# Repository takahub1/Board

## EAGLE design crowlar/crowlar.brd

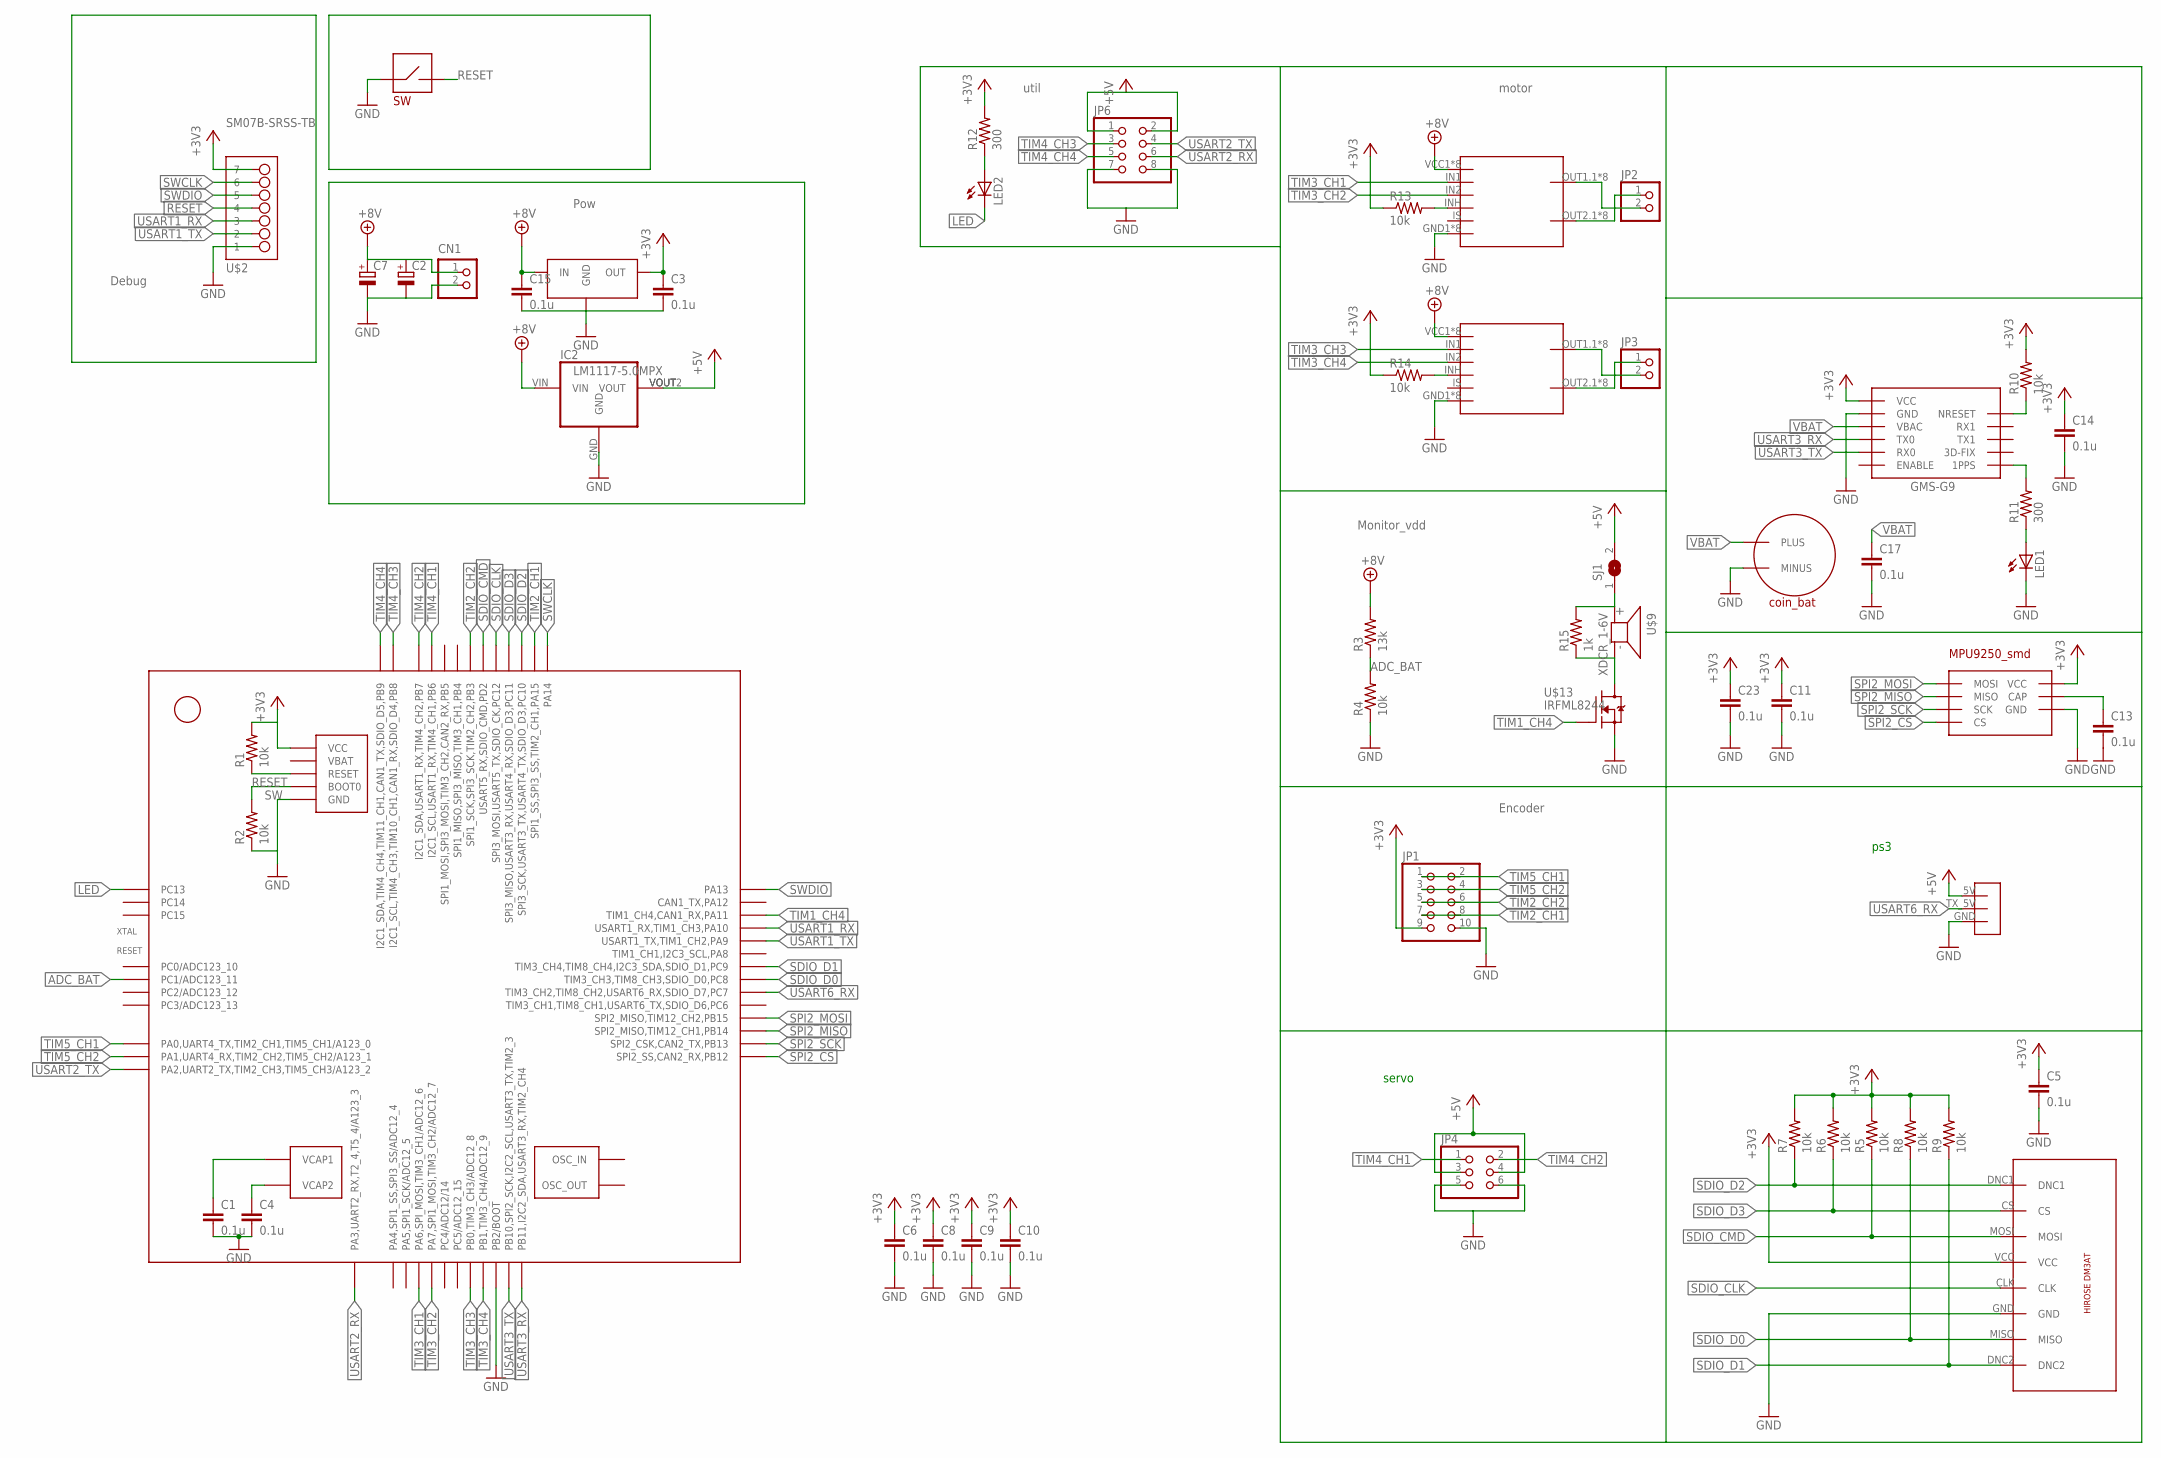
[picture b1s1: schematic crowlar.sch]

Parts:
C1, C3, C4, C5, C6, C8, C9, C10, C11, C13, C14, C15, C17, C23: 0.1u; C0603K
C2, C7: CPOL-EU153CLV-0605; 153CLV-0605
CN1: S2B-XASK-1
IC2: LM1117-5.0MPX; SOT223
JP1: PINHD-2X5/90; 2X05/90
JP2, JP3: PINHD-1X2/90; 1X02/90
JP4: PINHD-2X3/90; 2X03/90
JP6: PINHD-2X4/90; 2X04/90
LED1, LED2: LEDCHIP-LED0603; CHIP-LED0603
R1, R2, R4, R5, R6, R7, R8, R9, R10, R13, R14: 10k; R0603
R3: 13k; R0603
R11, R12: 300; R0603
R15: 1k; R0603
SJ1: SJ
STM32F405RGT6: STM32F405_T; LQFP64
U$1: GMS-G9
U$2: SM07B-SRSS-TB
U$3: SBDBT_5V
U$4, U$11: BTM7752
U$5: DM3AT
U$6: SWTVBP06-B043CB-B; SW
U$8: AP7361-33E; SOT223
U$9: XDCR_1-6V
U$10: 36-3030-ND
U$13: IRFML8244; SOT23
U$16: MPU9250_SMD

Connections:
+3V3: C3.1, C5.1, C6.1, C8.1, C9.1, C10.1, C11.1, C14.1, C23.1, JP1.9, R1.2, R5.2, R6.2, R7.2, R8.2, R9.2, R10.2, R12.2, R13.1, R14.1, STM32F405RGT6.13 (VCC), STM32F405RGT6.19 (VCC), STM32F405RGT6.32 (VCC), STM32F405RGT6.48 (VCC), STM32F405RGT6.64 (VCC), U$1.VCC, U$2.P$7 (7), U$5.VCC, U$8.OUT, U$16.RESV (VCC), U$16.VDD (VCC), U$16.VDDIO (VCC)
+5V: IC2.VOUT, IC2.VOUT2 (VOUT), JP4.3, JP4.4, JP6.1, JP6.2, SJ1.2, U$3.5V
+8V: C2.+, C7.+, C15.1, CN1.1, IC2.VIN, R3.2, U$4.VCC1 (VCC), U$4.VCC2 (VCC), U$4.VCC3 (VCC), U$4.VCC4 (VCC), U$4.VCC5 (VCC), U$4.VCC6 (VCC), U$4.VCC7 (VCC), U$4.VCC8 (VCC), U$8.IN, U$11.VCC1 (VCC), U$11.VCC2 (VCC), U$11.VCC3 (VCC), U$11.VCC4 (VCC), U$11.VCC5 (VCC), U$11.VCC6 (VCC), U$11.VCC7 (VCC), U$11.VCC8 (VCC)
ADC_BAT: R3.1, R4.2, STM32F405RGT6.9 (PC1/ADC123_11)
GND: C1.2, C2.-, C3.2, C4.2, C5.2, C6.2, C7.-, C8.2, C9.2, C10.2, C11.2, C13.2, C14.2, C15.2, C17.2, C23.2, CN1.2, IC2.GND, JP1.10, JP4.5, JP4.6, JP6.7, JP6.8, LED1.C, R2.1, R4.1, STM32F405RGT6.12 (GND), STM32F405RGT6.18 (GND), STM32F405RGT6.28 (PB2/BOOT), STM32F405RGT6.63 (GND), U$1.GND, U$1.GND1 (GND), U$2.P$1 (1), U$3.GND, U$4.GND1 (GND), U$4.GND2 (GND), U$4.GND3 (GND), U$4.GND4 (GND), U$4.GND5 (GND), U$4.GND6 (GND), U$4.GND7 (GND), U$4.GND8 (GND), U$5.GND, U$6.P$1, U$8.GND1 (GND), U$8.GND2 (GND), U$10.MINUS, U$11.GND1 (GND), U$11.GND2 (GND), U$11.GND3 (GND), U$11.GND4 (GND), U$11.GND5 (GND), U$11.GND6 (GND), U$11.GND7 (GND), U$11.GND8 (GND), U$13.2 (S), U$16.GND, U$16.~RESV (GND)
LED: LED2.C, STM32F405RGT6.2 (PC13)
unnamed: JP2.1, U$4.OUT2.1 (OUT2), U$4.OUT2.2 (OUT2), U$4.OUT2.3 (OUT2), U$4.OUT2.4 (OUT2), U$4.OUT2.5 (OUT2), U$4.OUT2.6 (OUT2), U$4.OUT2.7 (OUT2), U$4.OUT2.8 (OUT2)
unnamed: R14.2, U$11.INH
unnamed: R13.2, U$4.INH
unnamed: JP2.2, U$4.OUT1.1 (OUT1), U$4.OUT1.2 (OUT1), U$4.OUT1.3 (OUT1), U$4.OUT1.4 (OUT1), U$4.OUT1.5 (OUT1), U$4.OUT1.6 (OUT1), U$4.OUT1.7 (OUT1), U$4.OUT1.8 (OUT1)
unnamed: C4.1, STM32F405RGT6.47 (VCAP2)
unnamed: C1.1, STM32F405RGT6.31 (VCAP1)
unnamed: R15.2, SJ1.1, U$9.PLUS
unnamed: R15.1, U$9.MINUS (2), U$13.3 (D)
unnamed: JP3.2, U$11.OUT1.1 (OUT1), U$11.OUT1.2 (OUT1), U$11.OUT1.3 (OUT1), U$11.OUT1.4 (OUT1), U$11.OUT1.5 (OUT1), U$11.OUT1.6 (OUT1), U$11.OUT1.7 (OUT1), U$11.OUT1.8 (OUT1)
unnamed: R10.1, U$1.NRESET
unnamed: R11.2, U$1.1PPS
unnamed: LED1.A, R11.1
unnamed: LED2.A, R12.1
unnamed: JP3.1, U$11.OUT2.1 (OUT2), U$11.OUT2.2 (OUT2), U$11.OUT2.3 (OUT2), U$11.OUT2.4 (OUT2), U$11.OUT2.5 (OUT2), U$11.OUT2.6 (OUT2), U$11.OUT2.7 (OUT2), U$11.OUT2.8 (OUT2)
unnamed: C13.1, U$16.REGOUT (CAP)
RESET: R1.1, STM32F405RGT6.7 (RESET), U$2.P$4 (4), U$6.P$2
SDIO_CLK: STM32F405RGT6.53 (SPI3_MOSI,USART5_TX,SDIO_CK,PC12), U$5.CLK
SDIO_CMD: R5.1, STM32F405RGT6.54 (USART5_RX,SDIO_CMD,PD2), U$5.MOSI
SDIO_D0: R8.1, STM32F405RGT6.39 (TIM3_CH3,TIM8_CH3,SDIO_D0,PC8), U$5.MISO
SDIO_D1: R9.1, STM32F405RGT6.40 (TIM3_CH4,TIM8_CH4,I2C3_SDA,SDIO_D1,PC9), U$5.DNC2
SDIO_D2: R7.1, STM32F405RGT6.51 (SPI3_SCK,USART3_TX,USART4_TX,SDIO_D3,PC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), U$5.DNC1
SDIO_D3: R6.1, STM32F405RGT6.52 (SPI3_MISO,USART3_RX,USART4_RX,SDIO_D3,P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), U$5.CS
SPI2_CS: STM32F405RGT6.33 (SPI2_SS,CAN2_RX,PB12), U$16.CS
SPI2_MISO: STM32F405RGT6.35 (SPI2_MISO,TIM12_CH1,PB14), U$16.MISO
SPI2_MOSI: STM32F405RGT6.36 (SPI2_MISO,TIM12_CH2,PB15), U$16.MOSI
SPI2_SCK: STM32F405RGT6.34 (SPI2_CSK,CAN2_TX,PB13), U$16.SCK
SW: R2.2, STM32F405RGT6.60 (BOOT0)
SWCLK: STM32F405RGT6.49 (PA14), U$2.P$6 (6)
SWDIO: STM32F405RGT6.46 (PA13), U$2.P$5 (5)
TIM1_CH4: STM32F405RGT6.44 (TIM1_CH4,CAN1_RX,PA11), U$13.1 (G)
TIM2_CH1: JP1.7, JP1.8, STM32F405RGT6.50 (SPI1_SS,SPI3_SS,TIM2_CH1,PA15)
TIM2_CH2: JP1.5, JP1.6, STM32F405RGT6.55 (SPI1_SCK,SPI3_SCK,TIM2_CH2,PB3)
TIM3_CH1: STM32F405RGT6.22 (PA6,SPI_MOSI,TIM3_CH1/ADC12_6), U$4.IN1
TIM3_CH2: STM32F405RGT6.23 (PA7,SPI1_MOSI,TIM3_CH2/ADC12_7), U$4.IN2
TIM3_CH3: STM32F405RGT6.26 (PB0,TIM3_CH3/ADC12_8), U$11.IN1
TIM3_CH4: STM32F405RGT6.27 (PB1,TIM3_CH4/ADC12_9), U$11.IN2
TIM4_CH1: JP4.1, STM32F405RGT6.58 (I2C1_SCL,USART1_RX,TIM4_CH1,PB6)
TIM4_CH2: JP4.2, STM32F405RGT6.59 (I2C1_SDA,USART1_RX,TIM4_CH2,PB7)
TIM4_CH3: JP6.3, STM32F405RGT6.61 (I2C1_SCL,TIM4_CH3,TIM10_CH1,CAN1_RX,SDI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)
TIM4_CH4: JP6.5, STM32F405RGT6.62 (I2C1_SDA,TIM4_CH4,TIM11_CH1,CAN1_TX,SDI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)
TIM5_CH1: JP1.1, JP1.2, STM32F405RGT6.14 (PA0,UART4_TX,TIM2_CH1,TIM5_CH1/A123_0)
TIM5_CH2: JP1.3, JP1.4, STM32F405RGT6.15 (PA1,UART4_RX,TIM2_CH2,TIM5_CH2/A123_1)
USART1_RX: STM32F405RGT6.43 (USART1_RX,TIM1_CH3,PA10), U$2.P$3 (3)
USART1_TX: STM32F405RGT6.42 (USART1_TX,TIM1_CH2,PA9), U$2.P$2 (2)
USART2_RX: JP6.6, STM32F405RGT6.17 (PA3,UART2_RX,T2_4,T5_4/A123_3)
USART2_TX: JP6.4, STM32F405RGT6.16 (PA2,UART2_TX,TIM2_CH3,TIM5_CH3/A123_2)
USART3_RX: STM32F405RGT6.30 (PB11,I2C2_SDA,USART3_RX,TIM2_CH4), U$1.TX0
USART3_TX: STM32F405RGT6.29 (PB10,SPI2_SCK,I2C2_SCL,USART3_TX,TIM2_3), U$1.RX0
USART6_RX: STM32F405RGT6.38 (TIM3_CH2,TIM8_CH2,USART6_RX,SDIO_D7,PC7), U$3.TX_5V
VBAT: C17.1, U$1.VBAC, U$10.PLUS1 (PLUS), U$10.PLUS2 (PLUS)

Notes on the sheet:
Debug
Pow
Encoder
Monitor_vdd
motor
util
ps3
servo

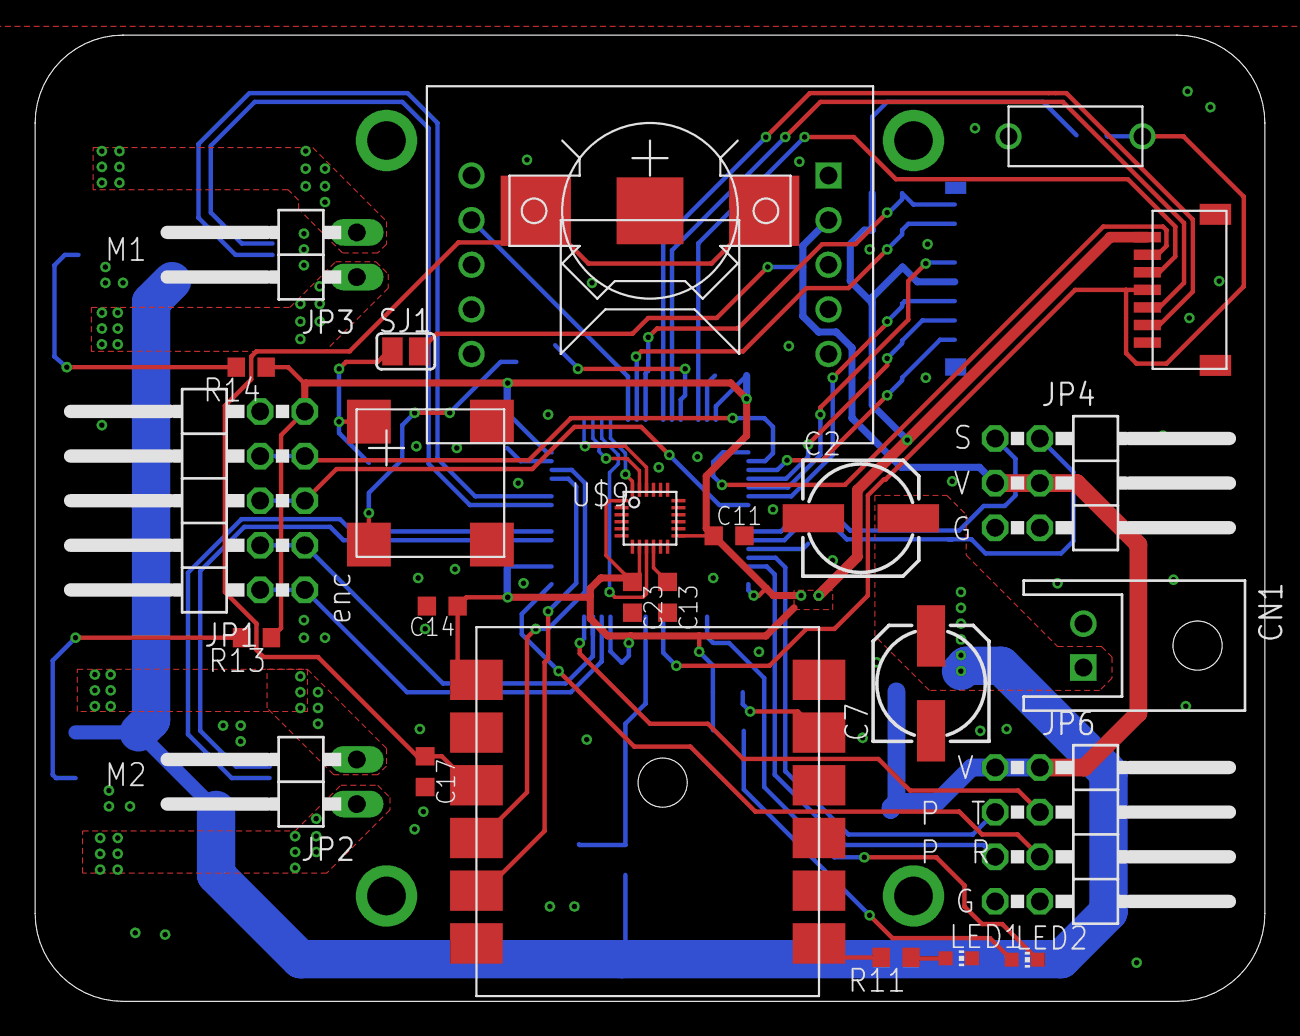
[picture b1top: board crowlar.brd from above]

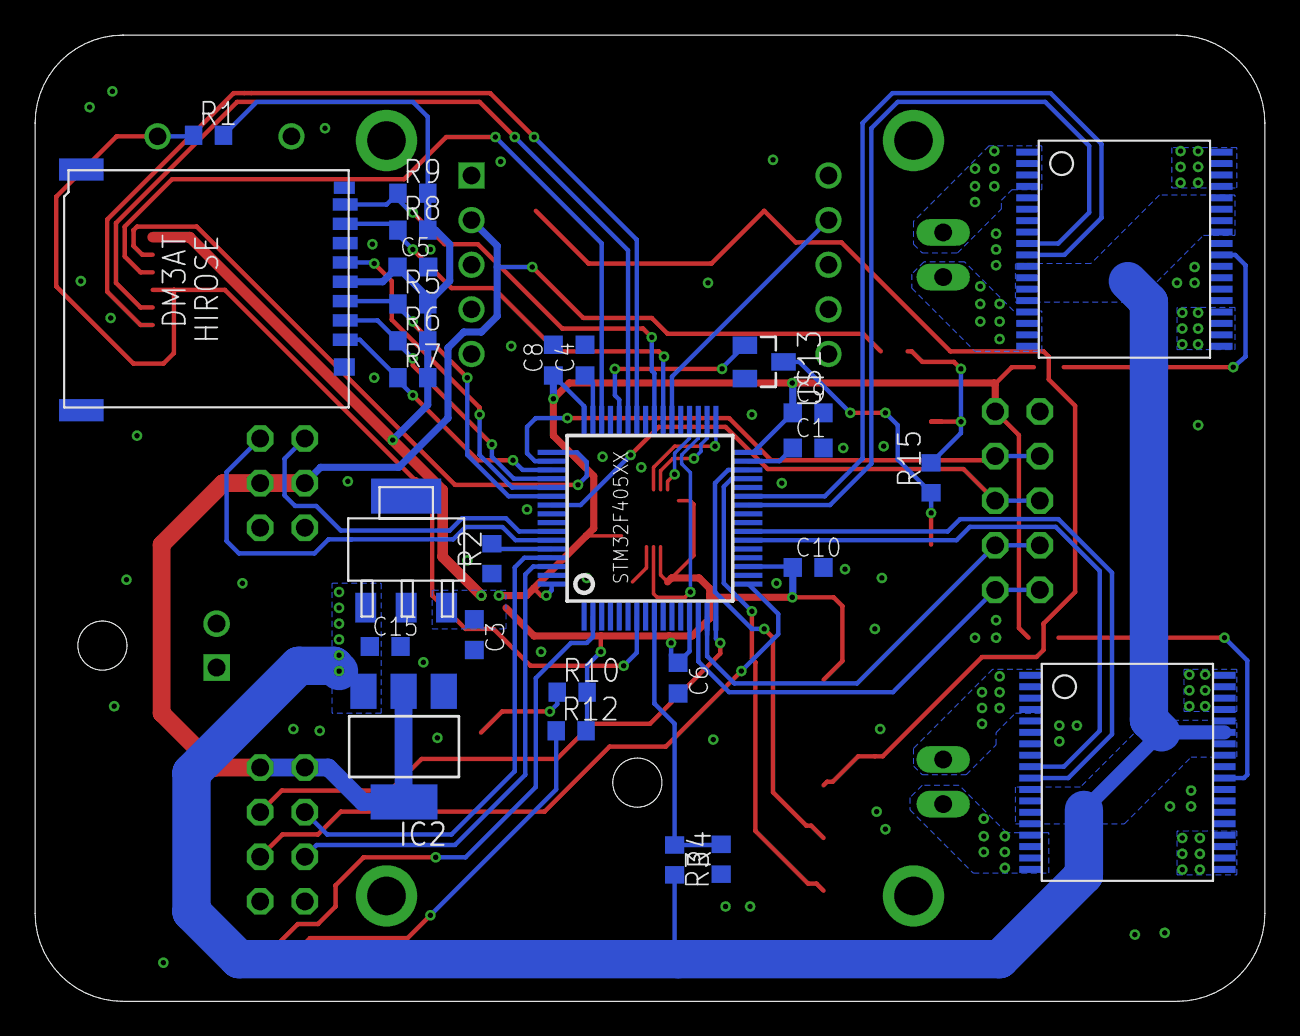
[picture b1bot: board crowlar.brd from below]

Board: 2 copper layers, 70.0 x 55.0 mm, 54 parts (28 on the bottom side), 56 nets.

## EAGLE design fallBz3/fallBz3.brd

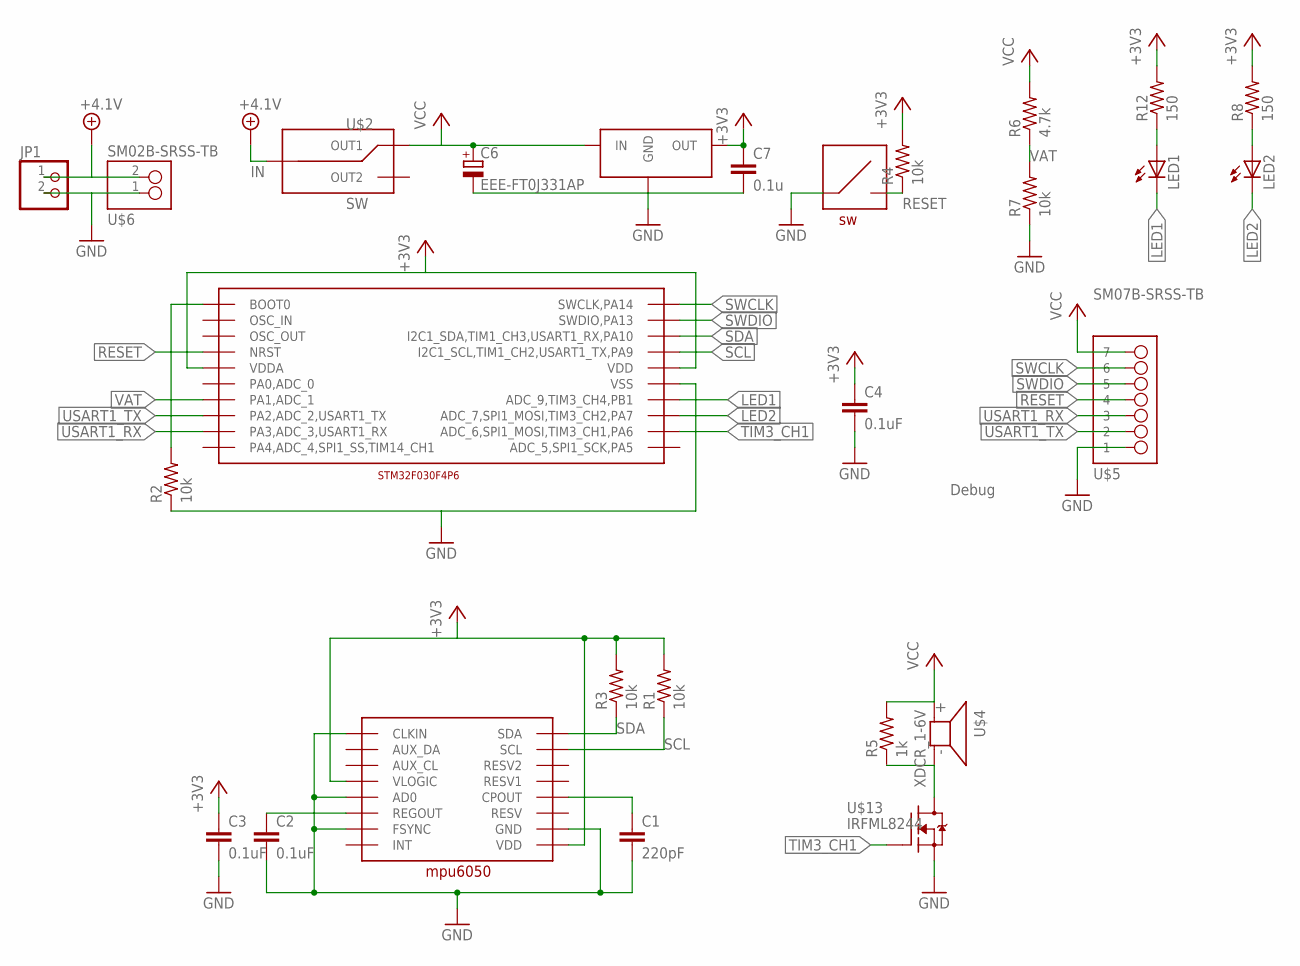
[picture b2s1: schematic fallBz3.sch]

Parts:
C1: 220pF; C0603K
C2, C3, C4: 0.1uF; C0603K
C6: EEE-FT0J331AP; 153CLV-0605
C7: 0.1u; C0603K
JP1: PINHD-1X2; 1X02
LED1, LED2: LEDCHIP-LED0603; CHIP-LED0603
R1, R2, R3, R4, R7: 10k; R0603
R5: 1k; R0603
R6: 4.7k; R0603
R8, R12: 150; R0603
U$1: STM-TSSOP20
U$2: SW; SS-12D00
U$3: MPU6050
U$4: XDCR_1-6V
U$5: SM07B-SRSS-TB
U$6: SM02B-SRSS-TB
U$7: KMT071-NGJ-LHS
U$8: AP7361-33E; SOT223
U$13: IRFML8244; SOT23

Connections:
+3V3: C3.1, C4.1, C7.1, R1.2, R3.2, R4.2, R8.2, R12.2, U$1.P$5 (VDDA), U$1.P$16 (VDD), U$3.VDD, U$3.VLOGIC, U$8.OUT
+4.1V: JP1.1, U$2.IN, U$6.2
GND: C1.2, C2.2, C3.2, C4.2, C6.-, C7.2, JP1.2, R2.1, R7.1, U$1.P$15 (VSS), U$3.AD0, U$3.CLKIN, U$3.FSYNC, U$3.GND, U$5.P$1 (1), U$6.1, U$7.SW00, U$7.SW0, U$8.GND1 (GND), U$8.GND2 (GND), U$13.2 (S)
LED1: LED1.C, U$1.P$14 (ADC_9,TIM3_CH4,PB1)
LED2: LED2.C, U$1.P$13 (ADC_7,SPI1_MOSI,TIM3_CH2,PA7)
unnamed: C2.1, U$3.REGOUT
unnamed: LED2.A, R8.1
unnamed: R5.1, U$4.MINUS (2), U$13.3 (D)
unnamed: C1.1, U$3.CPOUT
unnamed: R2.2, U$1.P$1 (BOOT0)
unnamed: LED1.A, R12.1
RESET: R4.1, U$1.P$4 (NRST), U$5.P$4 (4), U$7.SW1, U$7.SW11
SCL: R1.1, U$1.P$17 (I2C1_SCL,TIM1_CH2,USART1_TX,PA9), U$3.SCL
SDA: R3.1, U$1.P$18 (I2C1_SDA,TIM1_CH3,USART1_RX,PA10), U$3.SDA
SWCLK: U$1.P$20 (SWCLK,PA14), U$5.P$6 (6)
SWDIO: U$1.P$19 (SWDIO,PA13), U$5.P$5 (5)
TIM3_CH1: U$1.P$12 (ADC_6,SPI1_MOSI,TIM3_CH1,PA6), U$13.1 (G)
USART1_RX: U$1.P$9 (PA3,ADC_3,USART1_RX), U$5.P$3 (3)
USART1_TX: U$1.P$8 (PA2,ADC_2,USART1_TX), U$5.P$2 (2)
VAT: R6.1, R7.2, U$1.P$7 (PA1,ADC_1)
VCC: C6.+, R5.2, R6.2, U$2.OUT1, U$4.PLUS, U$5.P$7 (7), U$8.IN

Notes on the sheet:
Debug

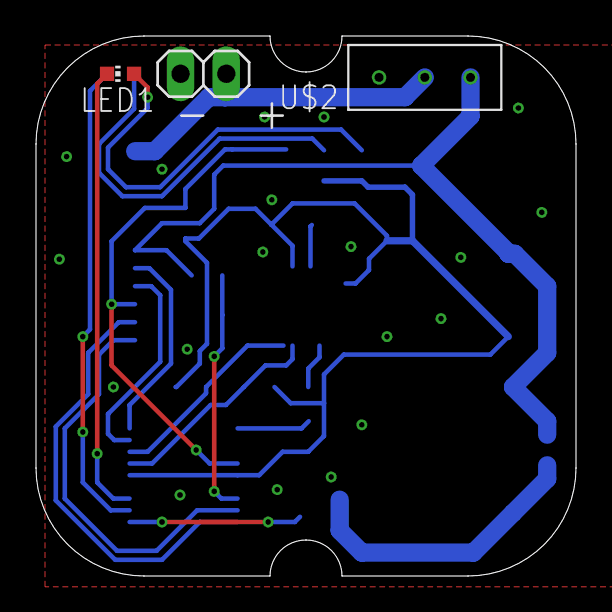
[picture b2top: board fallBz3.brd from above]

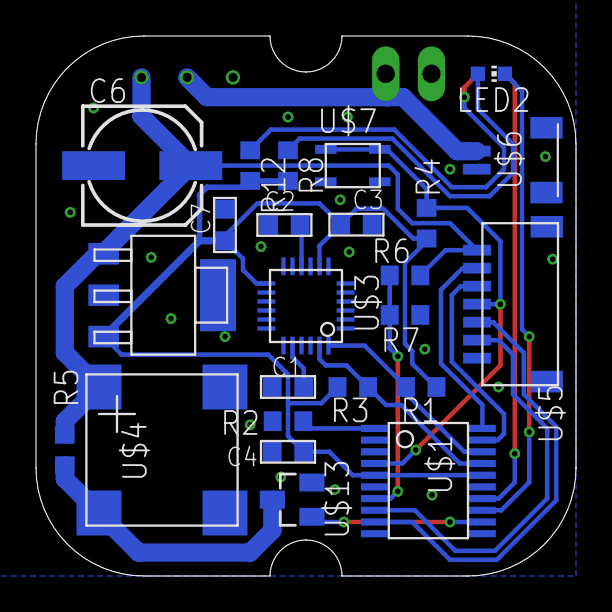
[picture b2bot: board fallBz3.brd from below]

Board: 2 copper layers, 30.0 x 30.0 mm, 27 parts (24 on the bottom side), 21 nets.

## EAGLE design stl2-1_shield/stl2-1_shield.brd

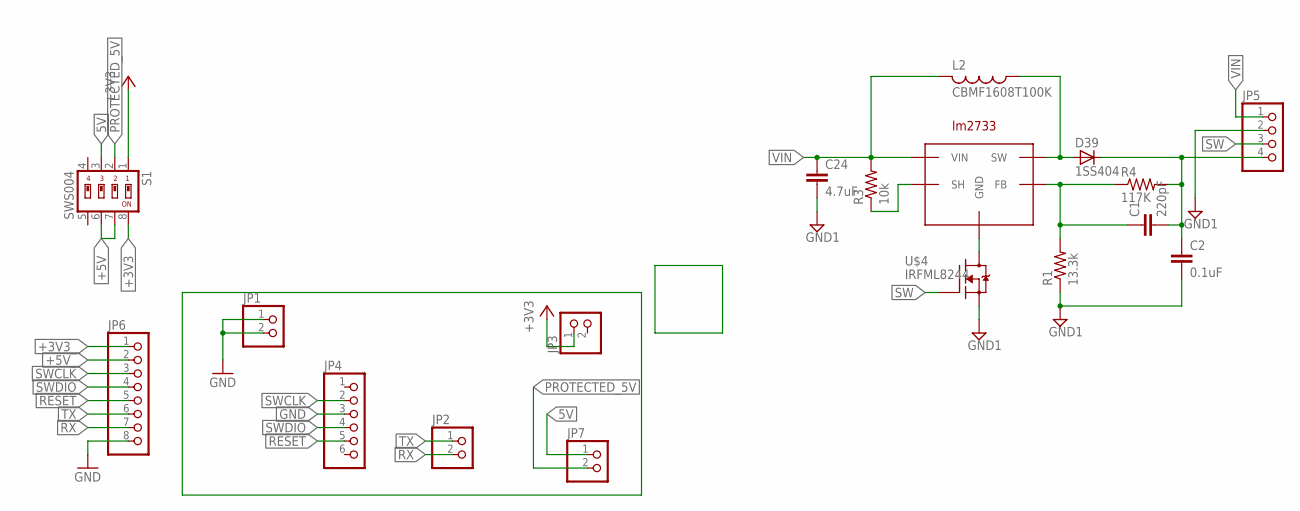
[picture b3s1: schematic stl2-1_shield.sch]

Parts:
C1: 220pF; C0603K
C2: 0.1uF; C0603K
C24: 4.7uF; C0603K
D39: 1SS404; USC(1.25X2.5)
JP1, JP2, JP3, JP7: PINHD-1X2; 1X02
JP4: PINHD-1X6; 1X06
JP5: PINHD-1X4; 1X04
JP6: PINHD-1X8/90; 1X08/90
L2: CBMF1608T100K; L2012C
R1: 13.3k; R0603
R3: 10k; R0603
R4: 117K; R0603
S1: SWS004; SMS-004
U$1: LM2733; SOT23-5
U$4: IRFML8244; SOT23

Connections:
5V: JP7.1, S1.3
+3V3: JP3.1, S1.1
+3V3_: JP6.1, S1.8
+5V_: JP6.2, S1.6, S1.7
GND: JP1.1, JP1.2, JP4.3, JP6.8
GND1: C2.2, C24.2, JP5.2, R1.1, U$4.2 (S)
unnamed: D39.A, L2.1, U$1.SW
unnamed: R3.1, U$1.SH
unnamed: C1.2, C2.1, D39.K (C), JP5.4, R4.2
unnamed: C1.1, R1.2, R4.1, U$1.FB
unnamed: U$1.GND, U$4.3 (D)
PROTECTED_5V: JP7.2, S1.2
RESET: JP4.5, JP6.5
RX: JP2.2, JP6.7
SW: JP5.3, U$4.1 (G)
SWCLK: JP4.2, JP6.3
SWDIO: JP4.4, JP6.4
TX: JP2.1, JP6.6
VIN: C24.1, JP5.1, L2.2, R3.2, U$1.VIN

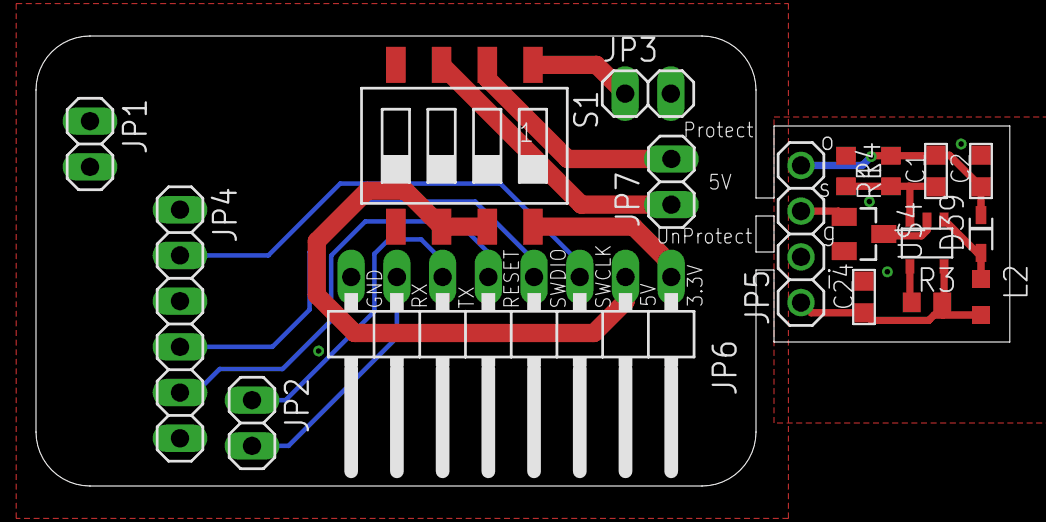
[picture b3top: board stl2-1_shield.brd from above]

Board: 2 copper layers, 54.1 x 25.0 mm, 18 parts (0 on the bottom side), 19 nets.

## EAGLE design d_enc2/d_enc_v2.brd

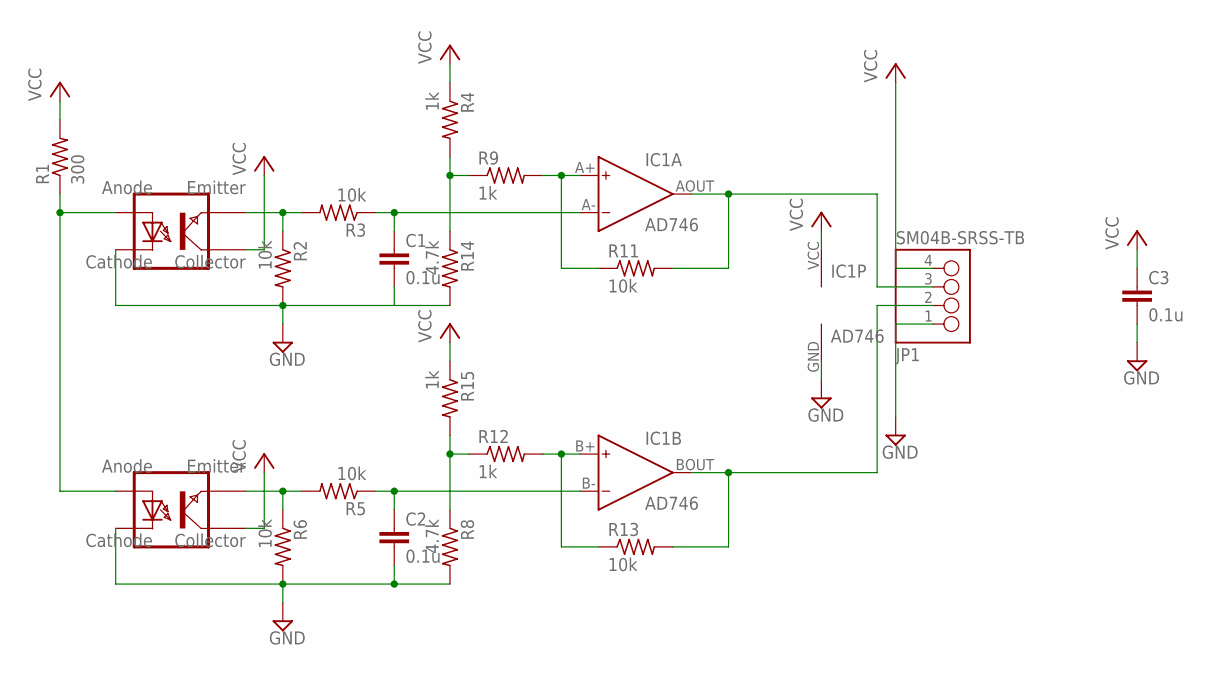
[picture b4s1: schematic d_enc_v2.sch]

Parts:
C1, C2, C3: 0.1u; C0603
IC1: AD746; NJM2903E
JP1: SM04B-SRSS-TB
R1: 300; R0603
R2, R3, R5, R6, R11, R13: 10k; R0603
R4, R9, R12, R15: 1k; R0603
R8, R14: 4.7k; R0603
U$1, U$4: TPR-105F

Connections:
GND: C1.2, C2.2, C3.2, IC1.GND (V-), JP1.1, R2.2, R6.2, R8.2, R14.2, U$1.CATHODE, U$4.CATHODE
unnamed: C1.1, IC1.A- (IN-), R3.1
unnamed: R1.1, U$1.ANODE, U$4.ANODE
unnamed: R2.1, R3.2, U$4.EMITTER
unnamed: R5.2, R6.1, U$1.EMITTER
unnamed: IC1.A+ (IN+), R9.2, R11.1
unnamed: C2.1, IC1.B- (IN-), R5.1
unnamed: IC1.AOUT (OUT), JP1.3, R11.2
unnamed: IC1.BOUT (OUT), JP1.2, R13.2
unnamed: R8.1, R12.1, R15.2
unnamed: IC1.B+ (IN+), R12.2, R13.1
unnamed: R4.2, R9.1, R14.1
VCC: C3.1, IC1.VCC (V+), JP1.4, R1.2, R4.1, R15.1, U$1.COLLECTOR, U$4.COLLECTOR

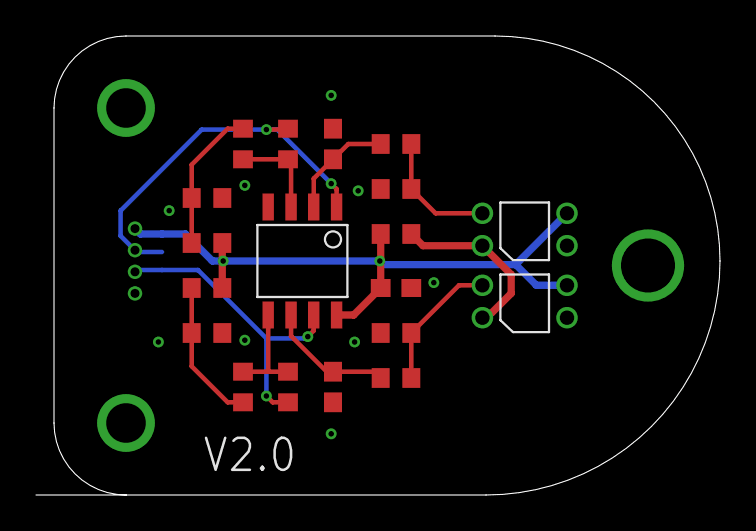
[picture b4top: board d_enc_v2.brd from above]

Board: 2 copper layers, 38.0 x 25.5 mm, 20 parts (1 on the bottom side), 13 nets.

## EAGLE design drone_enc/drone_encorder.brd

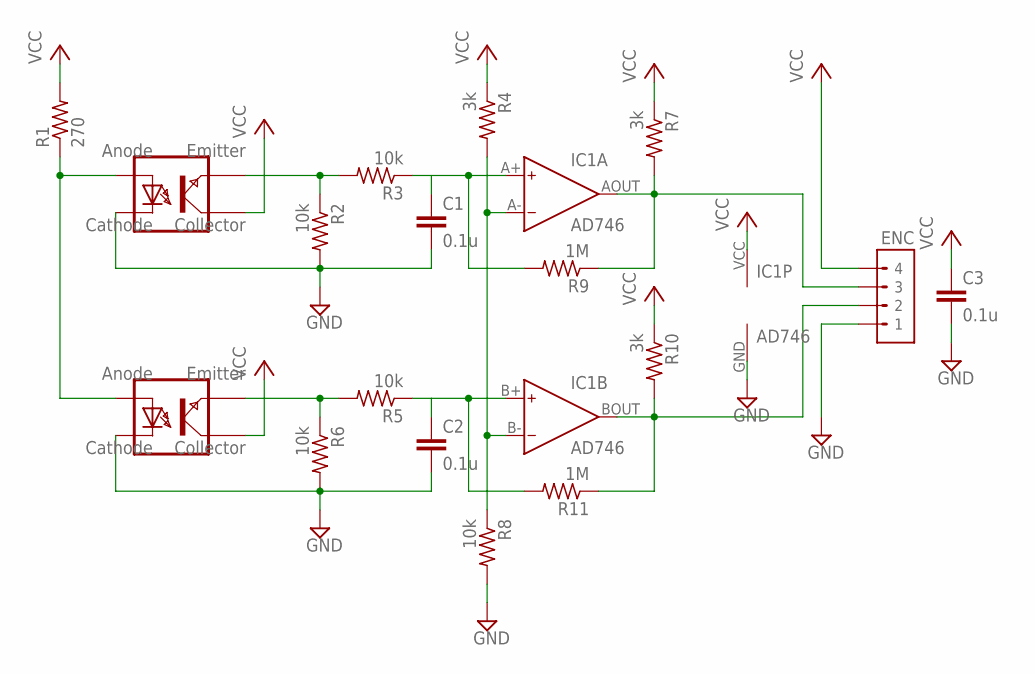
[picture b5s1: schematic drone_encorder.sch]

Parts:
C1, C2, C3: 0.1u; C0603
ENC: TOP_TYPE_4PIN
IC1: AD746; NJM2903E
R1: 270; R0603
R2, R3, R5, R6, R8: 10k; R0603
R4, R7, R10: 3k; R0603
R9, R11: 1M; R0603
U$1, U$4: TPR-105F

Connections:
GND: C1.2, C2.2, C3.2, ENC.1, IC1.GND (V-), R2.2, R6.2, R8.2, U$1.CATHODE, U$4.CATHODE
unnamed: C1.1, IC1.A+ (IN+), R3.1, R9.2
unnamed: R1.1, U$1.ANODE, U$4.ANODE
unnamed: R2.1, R3.2, U$4.EMITTER
unnamed: R5.2, R6.1, U$1.EMITTER
unnamed: IC1.A- (IN-), IC1.B- (IN-), R4.2, R8.1
unnamed: C2.1, IC1.B+ (IN+), R5.1, R11.2
unnamed: ENC.3, IC1.AOUT (OUT), R7.2, R9.1
unnamed: ENC.2, IC1.BOUT (OUT), R10.2, R11.1
VCC: C3.1, ENC.4, IC1.VCC (V+), R1.2, R4.1, R7.1, R10.1, U$1.COLLECTOR, U$4.COLLECTOR

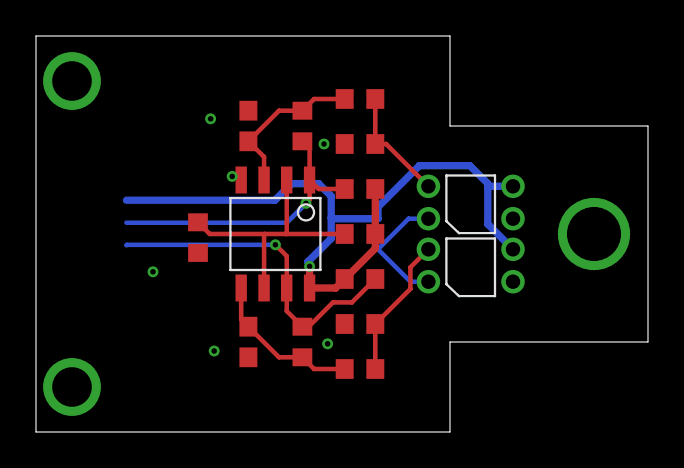
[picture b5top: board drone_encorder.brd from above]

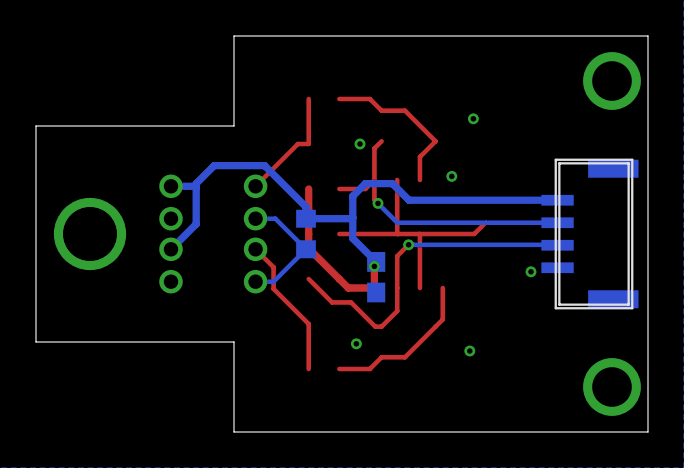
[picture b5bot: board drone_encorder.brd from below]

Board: 2 copper layers, 34.0 x 22.0 mm, 18 parts (3 on the bottom side), 10 nets.
